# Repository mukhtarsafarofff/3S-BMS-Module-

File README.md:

(ENG)  The function of this circuit is to charge the batteries, protect them for overvoltage, limit the current and also balance the batteries in case of more than one cell. Lithium ion or LiPo batteries are verry popular, especially with makers like us for small robots, portable devices, RC toy cars and drones and so on. But these batteries are also very sensible and dangerous. If we don’t control the process of charging anddischarging of such batteries, they will stop working or worse. The battery cells can swell and even explode from overcharging, and a deep discharge can make the battery fail. That’s why these batteries should go together with a battery management system unit or BMS. This will control the voltage and current from the battery and keep them safe. Usually, the nominal voltage of a LIPO battery is 3.8 volts and 4.2V when fully charged. As soon as the battery cell will reach this value, the charging process should stop and that’s what this circuit should do.  When we have only one cell, we only care about the maximum voltage and the current limit to protect the battery. But when we have a battery pack of more than 1 cell, so 2S, 3S and so on, we also need to balance the value of each individual cell. We have a PNP transistor connected in series with 4 diodes that will simulate a load. At the base of the transistor, we have a ZENNER reference diode (TL431) which will get open at a certain voltage value and by that connects ground to the transistors base and when the transistor is active, we bypass the battery and waste the power on the diodes instead. This ZENNER diode is the TL431 and it has a reference pin, so by adjusting the potentiometer we can set this reference to be at 4.2V, that’s how we select when the charging process will stop. I supply it with 4.2V from my power supply. I connect my multimeter at the output and using the potentiometer, we first fix the threshold value to around 4.16V, some value below 4.2V. I will use a battery which is discharged and below 4.2V (it was 3.8V). When I connect it to the charger, the LED is turned off. We have a current flow of around 450 mA and the battery is getting charged up. After some time, when we get above 4.16V the LED will turn ON so the charging process is complete. Current is now flowing through the diodes and transistor and we skip the battery, so the cell is protected for over voltage. I measure battery and it is 4.11 volts. We can take this simple circuit and merge it in series other identical circuits. With this circuit, we can charge a 3S battery for exampleand all individual cells will stop charging at 4.2V. The only downside, is the efficiency and heat dissipation. 

(DEU) Die Funktion dieses Schaltkreises besteht darin, die Batterien zu laden, sie vor Überspannung zu schützen, den Strom zu begrenzen und die Batterien bei mehr als einer Zelle auszugleichen. Lithium-Ionen- oder LiPo-Batterien sind sehr beliebt, besonders bei Machern wie uns für kleine Roboter, tragbare Geräte, ferngesteuerte Spielzeugautos und Drohnen und so weiter. Aber diese Batterien sind auch sehr empfindlich und gefährlich. Wenn wir den Lade- und Entladevorgang solcher Batterien nicht kontrollieren, werden sie nicht mehr funktionieren oder schlimmer.  Die Batteriezellen können sich aufblähen und sogar durch Überladung explodieren, und eine Tiefentladung kann die Batterie unbrauchbar machen. Deshalb sollten diese Batterien immer mit einem Batterie-Management-System (BMS) verwendet werden. Dieses kontrolliert die Spannung und den Strom der Batterie und hält sie sicher. Normalerweise beträgt die Nennspannung einer LiPo-Batterie 3,8 Volt und 4,2V, wenn sie vollständig geladen ist. Sobald die Batteriezelle diesen Wert erreicht, sollte der Ladevorgang gestoppt werden, und genau das soll dieser Schaltkreis tun. Wenn wir nur eine Zelle haben, kümmern wir uns nur um die maximale Spannung und die Strombegrenzung, um die Batterie zu schützen. Aber wenn wir einen Batteriepack mit mehr als einer Zelle haben, also 2S, 3S und so weiter, müssen wir auch den Wert jeder einzelnen Zelle ausgleichen. Wir haben einen PNP-Transistor, der in Reihe mit 4 Dioden geschaltet ist, die eine Last simulieren.  An der Basis des Transistors haben wir eine Zener-Diode (TL431), die sich bei einem bestimmten Spannungswert öffnet und dadurch die Basis des Transistors mit Masse verbindet. Wenn der Transistor aktiv ist, umgehen wir die Batterie und verschwenden die Energie stattdessen an den Dioden. Diese Zener-Diode ist die TL431 und sie hat einen Referenzpin, sodass wir durch Einstellen des Potentiometers diese Referenz auf 4,2V setzen können. So wählen wir den Zeitpunkt, wann der Ladevorgang gestoppt wird. Ich versorge den Schaltkreis mit 4,2V von meinem Netzteil. Ich schließe mein Multimeter am Ausgang an und stelle mit dem Potentiometer zuerst den Schwellenwert auf etwa 4,16V ein, also etwas unter 4,2V. Ich werde eine Batterie verwenden, die entladen ist und unter 4,2V liegt (sie hatte 3,8V). Wenn ich sie an das Ladegerät anschließe, ist die LED ausgeschaltet. Wir haben einen Stromfluss von etwa 450 mA und die Batterie wird aufgeladen. Nach einiger Zeit, wenn wir über 4,16V kommen, wird die LED einschalten, sodass der Ladevorgang abgeschlossen ist. Der Strom fließt jetzt durch die Dioden und den Transistor, und wir umgehen die Batterie, sodass die Zelle vor Überspannung geschützt ist.

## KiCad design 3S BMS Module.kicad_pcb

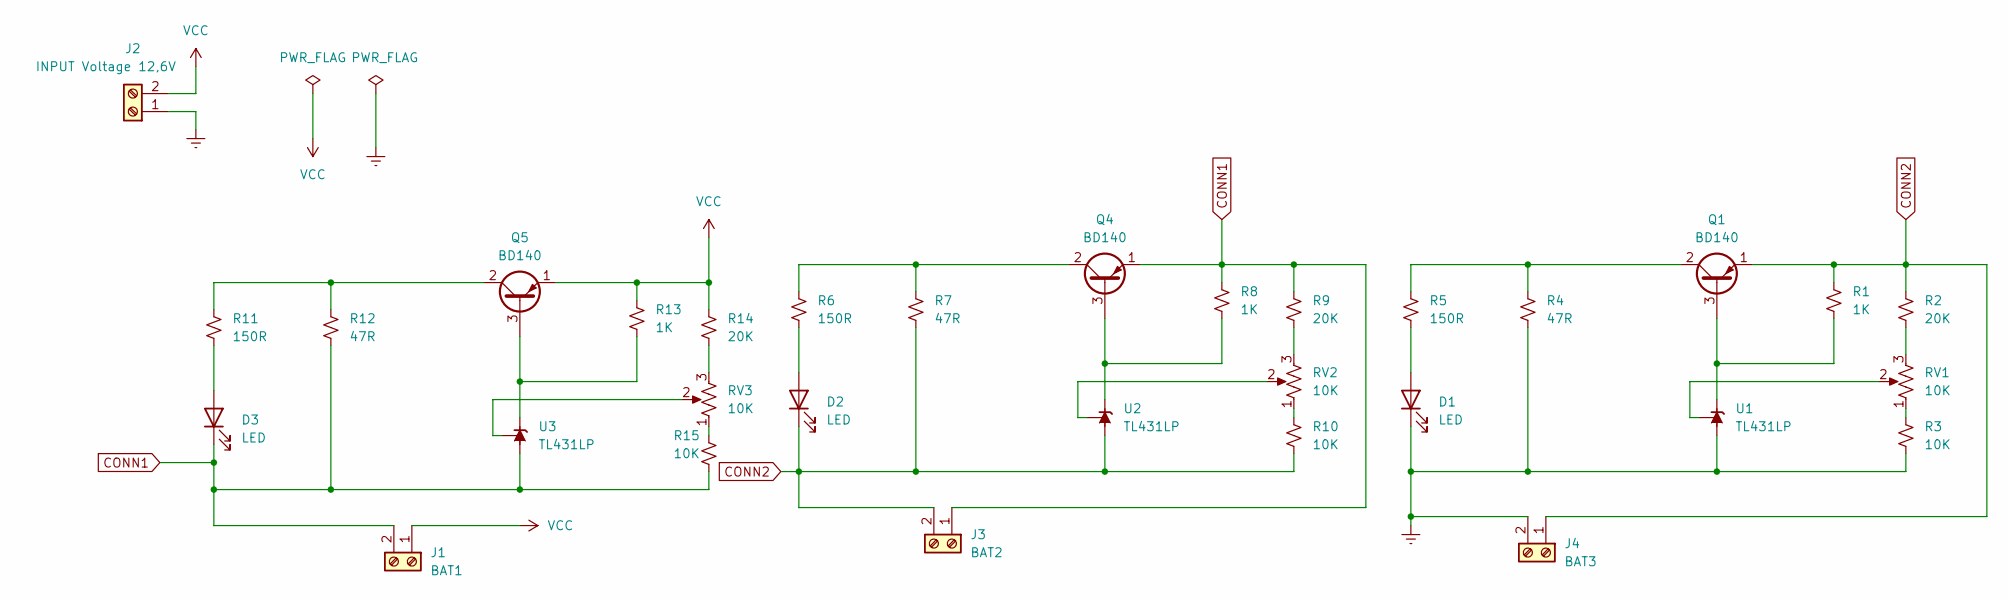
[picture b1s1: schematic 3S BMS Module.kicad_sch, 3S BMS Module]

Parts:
D1, D2, D3: LED; LED_D5.0mm
J1: BAT1; TerminalBlock_bornier-2_P5.08mm
J2: INPUT Voltage 12,6V; TerminalBlock_bornier-2_P5.08mm
J3: BAT2; TerminalBlock_bornier-2_P5.08mm
J4: BAT3; TerminalBlock_bornier-2_P5.08mm
Q1, Q4, Q5: BD140; TO-126-3_Vertical
R1, R8, R13: 1K; R_Axial_DIN0207_L6.3mm_D2.5mm_P15.24mm_Horizontal
R2, R9, R14: 20K; R_Axial_DIN0207_L6.3mm_D2.5mm_P15.24mm_Horizontal
R3, R10, R15: 10K; R_Axial_DIN0207_L6.3mm_D2.5mm_P15.24mm_Horizontal
R4, R7, R12: 47R; R_Axial_Power_L25.0mm_W9.0mm_P30.48mm
R5, R6, R11: 150R; R_Axial_DIN0207_L6.3mm_D2.5mm_P15.24mm_Horizontal
RV1, RV2, RV3: 10K; Potentiometer_Vishay_148-149_Single_Horizontal
U1, U2, U3: TL431LP; TO-92_Inline

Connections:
CONN1: D3.1 (K), J1.2, J3.1, Q4.1 (E), R8.1, R9.1, R12.2, R15.1, U3.2 (A)
CONN2: D2.1 (K), J3.2, J4.1, Q1.1 (E), R1.1, R2.1, R7.2, R10.1, U2.2 (A)
Earth: D1.1 (K), J2.1, J4.2, R3.1, R4.2, U1.2 (A)
unnamed: D1.2 (A), R5.2
unnamed: D2.2 (A), R6.2
unnamed: D3.2 (A), R11.2
unnamed: Q1.3 (B), R1.2, U1.3 (K)
unnamed: Q1.2 (C), R4.1, R5.1
unnamed: Q4.3 (B), R8.2, U2.3 (K)
unnamed: Q4.2 (C), R6.1, R7.1
unnamed: Q5.3 (B), R13.2, U3.3 (K)
unnamed: Q5.2 (C), R11.1, R12.1
unnamed: R2.2, RV1.3
unnamed: R3.2, RV1.1
unnamed: R9.2, RV2.3
unnamed: R10.2, RV2.1
unnamed: R14.2, RV3.3
unnamed: R15.2, RV3.1
unnamed: RV1.2, U1.1 (REF)
unnamed: RV2.2, U2.1 (REF)
unnamed: RV3.2, U3.1 (REF)
VCC: J1.1, J2.2, Q5.1 (E), R13.1, R14.1

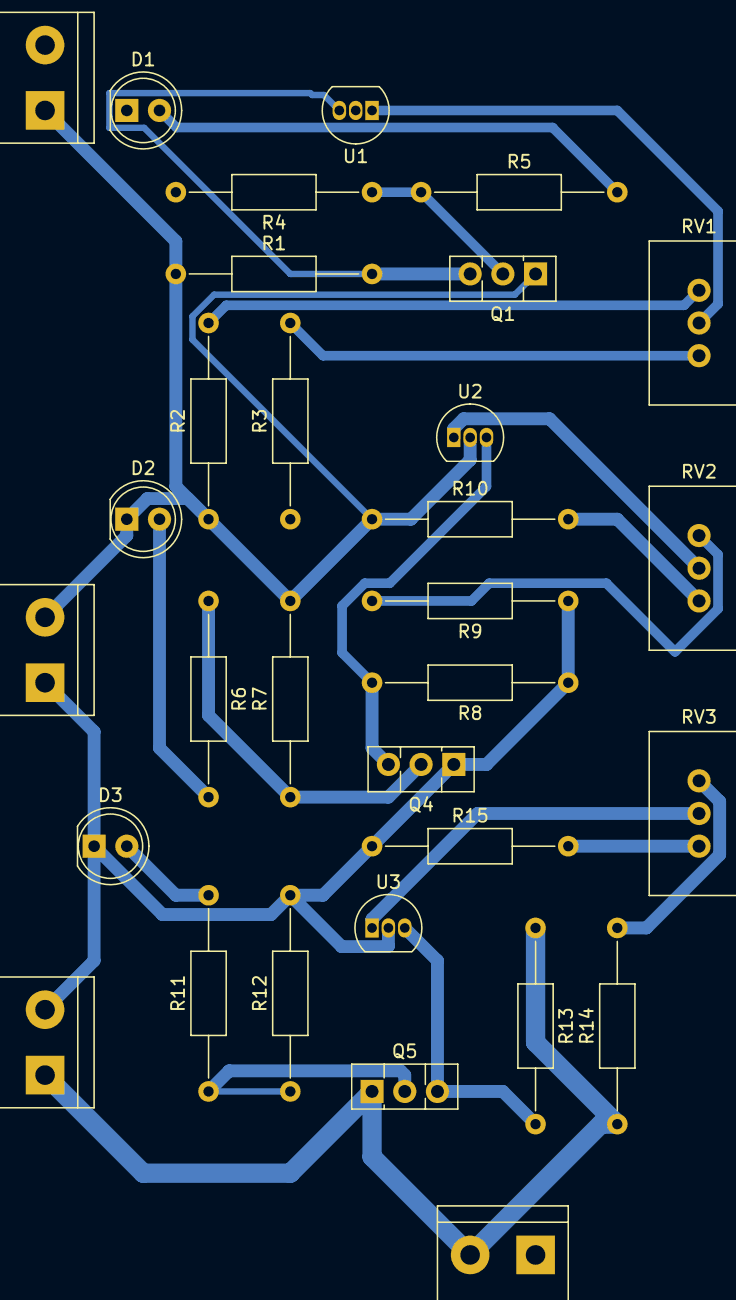
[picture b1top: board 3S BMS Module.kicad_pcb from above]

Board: 2 copper layers, 31 parts (0 on the bottom side), 22 nets.

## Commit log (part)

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2024-03-24 3S BMS Module is accomplished
2024-08-05 Update README.md]
